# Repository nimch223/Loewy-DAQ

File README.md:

# Loewy-DAQ
  
Visit our research group website: https://www.lehighloewyinstitute.org  

**Loewy-DAQ** Contains the work of Lehigh University Loewy Institute undergraduate researcher Nicholas Cheney on the development of a chatter monitoring / DAQ system for a 4-high rolling mill. This forms the basis of a project which will be iterated on by future students; the idea is to make use of signal processing in combination with the metal rolling process in order to detect, predict, and respond to incidences of chatter. 

"Guide for Next User" follows, below: 

---
# **Guide for Next User - Vibrational Analysis for a Four-High Rolling Mill**
### **Author**: Nicholas Cheney @nimch223  
### **Advisors**: Professor Wojtek Misiolek & Nick Rockwell @nmrockwell 
### **Document Last Updated On**: January 15, 2024

---

# **Table of Contents:**
+ **[Background](#background)**
+ **[I. Set Up Hardware](#i-set-up-hardware)**  
+ **[II. Download Software: MATLAB & Simulink](#ii-download-software-matlab--simulink)**  
+ **[III. Open & Configure Software](#iii-open--configure-software)**  
+ **[IV. Run Software](#iv-run-software)**  
+ **[V. Additional Information & Future Recommendations](#v-additional-information--future-recommendations)**  
+ **[Papers Referenced](#papers-referenced)**

---

## Background  
Using two ADXL345 accelerometers connected to an Adafruit METRO (a microcontroller that
is equivalent to the Arduino Uno), vibrational analysis of a four high rolling mill can be
performed. The two accelerometers in their housings are to be mounted on the upper backup
roll and top housing of the rolling mill in Whitaker 165.
  
 These two locations for the placement of
the accelerometers were chosen based on a literature review in which it was discovered that
the upper backup roll and top housing demonstrate a higher sensitivity to chatter, making them
ideal locations for the permanent installation of acceleration sensors [Niroomand et al. 864].
  
The accelerometers measure the vertical vibration of the mill for the presence of chatter, the
intense and undesirable vibration of the mill that can negatively impact the rollers and affect
the quality of the rolled material. The most destructive forms of chatter occur at the third and
fifth octave modes of vibration, 100 - 200 Hz and 500 - 700 Hz respectively [Choudhary et al.
1].   

At third octave chatter conditions, the rolled sample experiences poor surface finish quality
and variations in thickness, while at fifth octave chatter conditions the sample experiences
even worse surface finish, larger variations in thickness and potential rupture of the sample,
and the backup and work rolls can experience transverse bending. 

The goal in installing these
vibrational sensors on the rolling mill in Whitaker 165 is to better understand the relationship
between the vibration of a one-stand mill and the quality of rolled samples, and if chatter
occurs, catch it with live vibrational monitoring before it becomes destructive to the sample and
rolls. The following document goes through the process of procuring, manufacturing, and
setting up the hardware for the vibrational sensors, and walks through the steps of how to
configure and run the software for plotting the vibrational data from the two accelerometers. 

--- 

## I. Set Up Hardware  

The following components outline the hardware used to make the vibrational sensor. Included
are either the links of where to find and buy them, or the files where they can be located.  

Files located in Github, at the following location: https://github.com/nimch223/Loewy-DAQ

**1. Microcontroller:**  
- Adafruit METRO 
  - Link: https://www.adafruit.com/product/2488
- Clear Housing for METRO
  - Link: https://www.adafruit.com/product/3597?gad_source=1&gclid=Cj0KCQiAm
4WsBhCiARIsAEJIEzXbmyYK6P6f_sxl3pgHApCRhQQjLrS05EgrbCzs6rN
KPTvZjAyUd0QaAgsNEALw_wcB

**2. Accelerometers:**  
- (x2) Adafruit ADXL345 Accelerometers
  - Link: https://www.adafruit.com/product/1231  

- (x2) 3D-Printed Housing for ADXL345  
  - These housings were designed in SolidWorks to perfectly fit the ADXL345, as no
CAD files could be found online for the current ADXL345 accelerometer model.
Two housings were then printed out of PLA in Wilbur Powerhouse using the FDM
printers.

    - STL File (in this Github repo) for 3D printing: **ADXL345_housing.STL**
    - SolidWorks File (also in this Github repo)--if needed to edit: **ADXL345_housing.SLDPRT**  

- (x4) Screws needed to secure each ADXL345 in housing

**3. Printed Circuit Board (PCB):**  
- The PCB was designed in Autodesk EAGLE, a free and intuitive PCB design software.
The physical board was then manufactured in the Electronics Design Lab in Wilbur
Powerhouse using the Othermill V2 CNC Mill. Using the soldering iron in Wilbur, four
10kΩ resistors and break-away male headers were soldered onto the board, shown in
**Figure 6**.

    - Autodesk EAGLE Files (in this Github repository):
      - Schematic File: **PCB_for_ADXL345.sch**  
      - Board File: **PCB_for_ADXL345.brd**

**4. Wires / Cables:**
- (x4) female-to-male (F/M) jumper wires - used to connect the Arduino to one side of the PCB.
  - These can be seen in **Figure 7**, labeled "3".
    - Link: https://www.adafruit.com/product/1953?gad_source=1&gclid=Cj0KCQiAm4WsBhCiARIsAEJIEzUyF3oqaQGZTwtKFuOSnZRV7XU1m5S8ml8urbqnD2HHYeW__Y-boksaAtEdEALw_wcB

- (x2) female-to-female (F/F) cables.
  - Each cable is roughly 5.5 feet and has 6 female header contacts on each side. Each cable is used to connect the 6 pins on the ADXL345 accelerometer (highlighted in **Figure 2**) to the respective header
on the PCB (labeled "ADXL345_1" and "ADXL345_2" on the schematic in **Figure 5**).
These were spliced and made in the electronics lab in Wilbur Powerhouse.

---

## II. Download Software: MATLAB & Simulink  

1. Open the following link: https://matlab.mathworks.com/  
2. Click "Install MATLAB", located at the top right of the page.  
3. Double-click the ".dmg" file that is downloaded onto your ocmputer and follow the steps to finish installation. 
- When asked, install both "MATLAB" and "Simulink". 
- When "Installation Complete" message appears, if prompted, install a supported C compiler for your machine by clicking the link.
  - For Macintosh users, you need at least **Xcode 14.x**
    - For Apple users:
      - Visit https://developer.apple.com/download/more/ and sign into Apple ID.
      - In the search bar, look up "Xcode"
      - Download the most recent version, or the most recent version supported by your machine (for me, Xcode 14.2)
        - Check minimum requirements here: https://developer.apple.com/support/xcode/
      - Launch Xcode, install necessary elements.

---  

## III. Open & Configure Software  

1. Double-click MATLAB to open the program.
2. In the main MATLAB window, search the top toolbar for "Add-Ons" and double-click it to select it. This is highlighted below in **Figure 8**:

3. The "Add-On Explorer" window should launch--use the search bar towards the top right, and search for "Arduino".
4. Pluf the microcontroller (METRO / Arduino) into the computer. Ensure it is getting power by making sure the onboard LED is lit.
5. Install the two support packages titled "Simulink Support Package for Arduino Hardware" and "MATLAB Support Package for Arduino Hardware" by clicking the respective titles, and selecting the "Add" blue button on the right side of the screen. Follow the instructions to download, and ensure that the microcontroller is recognized by the computer.
6. Once both support packages have been downloaded, they should have a green "Installed" message by their picture in the "Add-On Explorer", similar to the **Figure 9** below:  

7. Close the Add-On Explorer window.
8. In the main MATLAB window, search the top toolbar for "Simulink" and double-click it to launch. **Figure 10** below highlights the Simulink symbol in the toolbar:  

9. A new Simulink window should open.
10. Download the file titled **"Two_ADXL345_accell.slx"** from Github, and open the file in the Simulink window. The code should appear similar to **Figure 11** below:

11. In the Simulink window toolbar, verify that the following settings are configured as follows:
  - Under the "Simulation" tab, set "Stop Time" to "inf" (infinity)
  - Under the "Hardware" tab:
    - Select the "Hardware Board" dropdown menu, and click "Select Another Hardware Board". A "Configuration Parameters" window will appear, and in the "Hardware Implementation" tab, select the "Hardware board:" dropdown meny and select "Arduino Uno". Click "Apply" at the bottom right, then click "OK".
    - Ensure that the mode "Run on board" is selected.
    - Click on "Hardware Settings", and a "Configuration Parameters" window will appear. In the "Hardware Impplementation" tab, select the dropdown menu titled "Target hardware resources" nested in "Hardware board settings". Under the "Groups" ttle, select the "Host-board connection" tab.
    - Open your computer's terminal and type the following command:  
      `ls/vex/tty.*`
      This lists all the serial devices plugged into the computer. The Metro/Arduino should appear as the two serial ports:
      `/dev/tty.SLAB_USBtoUART` and `/dev/tty.usbserial-01C6018D`
      ...the latter, ending with "...018D", is the important one.
    - In the same "Host-board connection" tab, click the dropdown menu for "Set host COM port" and select "Manually select". Directly beneath in the "Host COM Port" dropdown, select `/dev/tty.usbserial-01C6018D/`. Ensure that it is the **`/dev/tty...`** selection and *NOT* the similarly named `/dev/cu...`.
    - Under the same "Groups" title, select the last tab, titled "External mode". Ensure the "Communication interface" dropdown selection is "XCP on Serial".

---  
## IV. Run Software  

1. Navigate back to the MATLAB main window.  
2. Type the following code into the editor window, labeled in Figure 12 below as (1), and then click "Run" labaled as (2):
    
```matlab
% MATLAB commands:
clear all;
clc;
clear a;
a = arduino; 
```

3. Navigate back to the Simulink window and click "Monitor & Tune" at the top.
4. The code will take some time to run; if it runs successfully, a "Stop" option will appear in the "Hardware" tab of the top toolbar, and "Data Inspector" to the right of it.
5. Click on Data Inspector and a "Simulation Data Inspector" window will appear. Initially, the data coming from the two accelerometers may be displayed on a single graph as 6 lines: "x", "y", and "z" data from each accelerometer.
6. To split the data from the two different accelerometers into two graphs, click the window icon, shown below in Figure 13 as the box highlighted and labeled as (1). Next, under "Basic layouts", select the option with a graph above and below, labeled (2) in **Figure 13** below:

7. Click the top graph, which is outlined in blue in Figure 14. Under the "Filter signals" dropdown menu on the left, select the checkbox of the 3rd signal from the 1st accelerometer. Ensure that all other signals are deselected. The "Simulation Data Inspector" window should appear in **Figure 14** below:

8. Click the bottom graph, then under the "Filter signals" dropdown menu on the left, select the checkbox of the 3rd signal from the 2nd accelerometer. Ensure that all other signals are deslected. The "Simulation Data Inspector" window should appear like **Figure 15** below:

9. Steps "7" and "8" ensure that only the z-axis (vertical) signal from each accelerometer is graphed. The two running graphs should now display vertical vibrational data from each accelerometer.
10. When finished with measuring the vibrational data, go to the Simulink window and click "Stop" in the toolbar.
11. To save the data from the graphs, go back to the "Simulation Data Inspector" window, and select the "Export" symbol on the left toolbar, shown in **Figure 16** below:

12. In the "Export" settings window:
    - For "Export:", choose to export only the "Selected runs and signals" for export.
    - For "To:", export the data as an Excel Workbook ".xlsx" file
    - Once the file is exported, the data should appear in your computer under the "MATLAB" folder, wherever that is located.  
  
---  
## V. Additional Information & Future Recommendations  

- The current Simulink code here on Githbu (**Two_ADXL345_accell.slx**) is relatively simple. As displayed in **Figure 11**, it is composed of two accelerometer data source blocks. These blocks are connected to a scope block, which allows for real time data visualization and the real time plotting of the vibrational data.
- These data source blocks are configured so that each block matches the respective I2C address of each accelerometer: **0x1D** and **0x53**.
  - The two accelerometers hooked up in the circuit are recognized under different addresses because one accelerometer's **SDO** pin is connected to **GND**, while the other accelerometer's **SDO** pin is not. This can be seen in **Figure 5** (the PCB schematic).
  - Double-click each accelerometer data source block to display these addresses
  - Double-clicking these blocks also displays additional parameters for the accelerometers that can be set. These parameters include important factors such as the range of acceleration that the accelerometers can measure, and the accelerometer output data rate. *These parameters should be adjusted based on further research and needs*.
  - For example, the accelerometer output data rate is automatically set at 12.5 Hz, which is not high enough for fast and accurate data streaming. The data rate can be adjusted to as high as 1600 Hz.
- This information regarding how the wiring of the pins should be configured in order to communicate with two accelerometers under two different I2C addresses was found in the ADXL345 data sheet. This data sheet, along with the Adafruit ADXL345 website that has pinout, wiring guides, example code, and more, are extremely informative and useful for understanding the capabilities and limitations of the accelerometers. The links are below:
  - ADXL345 Data Sheet: https://www.analog.com/media/en/technical-documentation/data-sheets/adxl345.pdf
 
  - ADXL345 webpage listing: https://learn.adafruit.com/adxl345-digital-accelerometer/overview  

- The need for additional processing, filtering, or denoising of the data may be discovered in the future. The MATLAB and Simulink software was chosen due to it being relatively simple, visual, and intuitive, and an easy base to build off of.
- In order to perform this additional data processing in Simulink, extra blocks would be added to the current Simulink model.
  - Based on the processing needs, pre-built data filtering blocks can be selected from Simulink's library.
  - These filtering blocks can be easily inserted between the accelerometer data source blocks and scope blocks--some examples of filter blocks that can be added are:
    - High pass filter block
    - Automatic gain control block
    - Low pass filter block
  - From the literature review, the aforementioned filters are recommended for data processing [Niroomand et al. 857]. **Figure 17** below shows a potential block diagram for data signal filtering and processing:

  - The process for the ADXL345 accelerometer would be similar to the process shown in **Figure 17** bit slightly different, as the accelerometers have a built in ADC, or "Analog to Digital (A/D) Converter".     
---  

## Papers Referenced  

1. Choudhary et al. “A Review on Chatter Analysis in Cold Rolling process.” Juniper Online
Journal Material Science, vol. 2, issue no. 1, 2017, page 1, ISSN 2575-856X.  

2. Niroomand et al. “Frequency analysis of chatter vibrations in tandem rolling mills.” Journal of
Vibroengineering, vol. 14, issue no. 2, 2012, pages 857 - 864, ISSN 1392-8716.

---

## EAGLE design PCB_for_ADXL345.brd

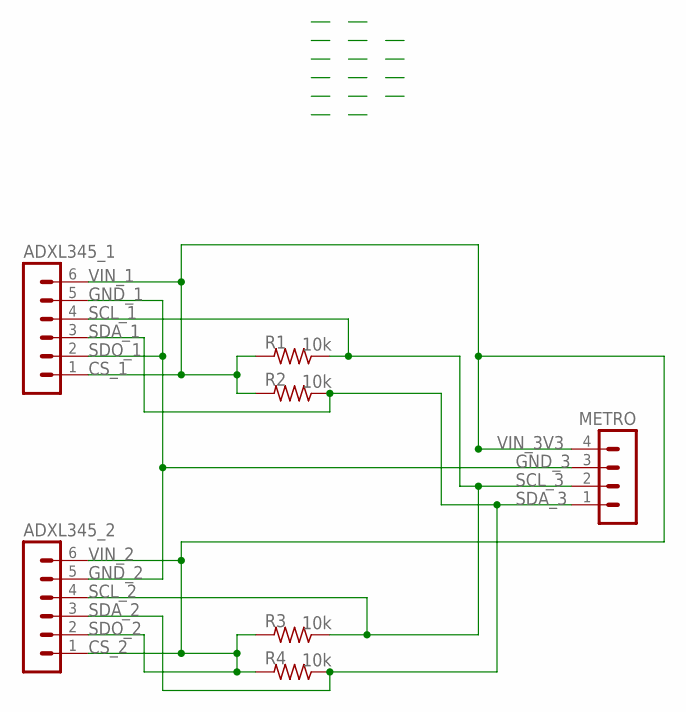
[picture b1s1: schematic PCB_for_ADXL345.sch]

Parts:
ADXL345_1, ADXL345_2: MA06-1
METRO: MA04-1
R1, R2, R3, R4: 10k; 0207/10

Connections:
GND: ADXL345_1.2, ADXL345_1.5, ADXL345_2.5, METRO.3
unnamed: ADXL345_1.3, ADXL345_2.3, METRO.1, R2.1, R4.1
unnamed: ADXL345_1.4, ADXL345_2.4, METRO.2, R1.1, R3.1
VIN: ADXL345_1.1, ADXL345_1.6, ADXL345_2.1, ADXL345_2.2, ADXL345_2.6, METRO.4, R1.2, R2.2, R3.2, R4.2

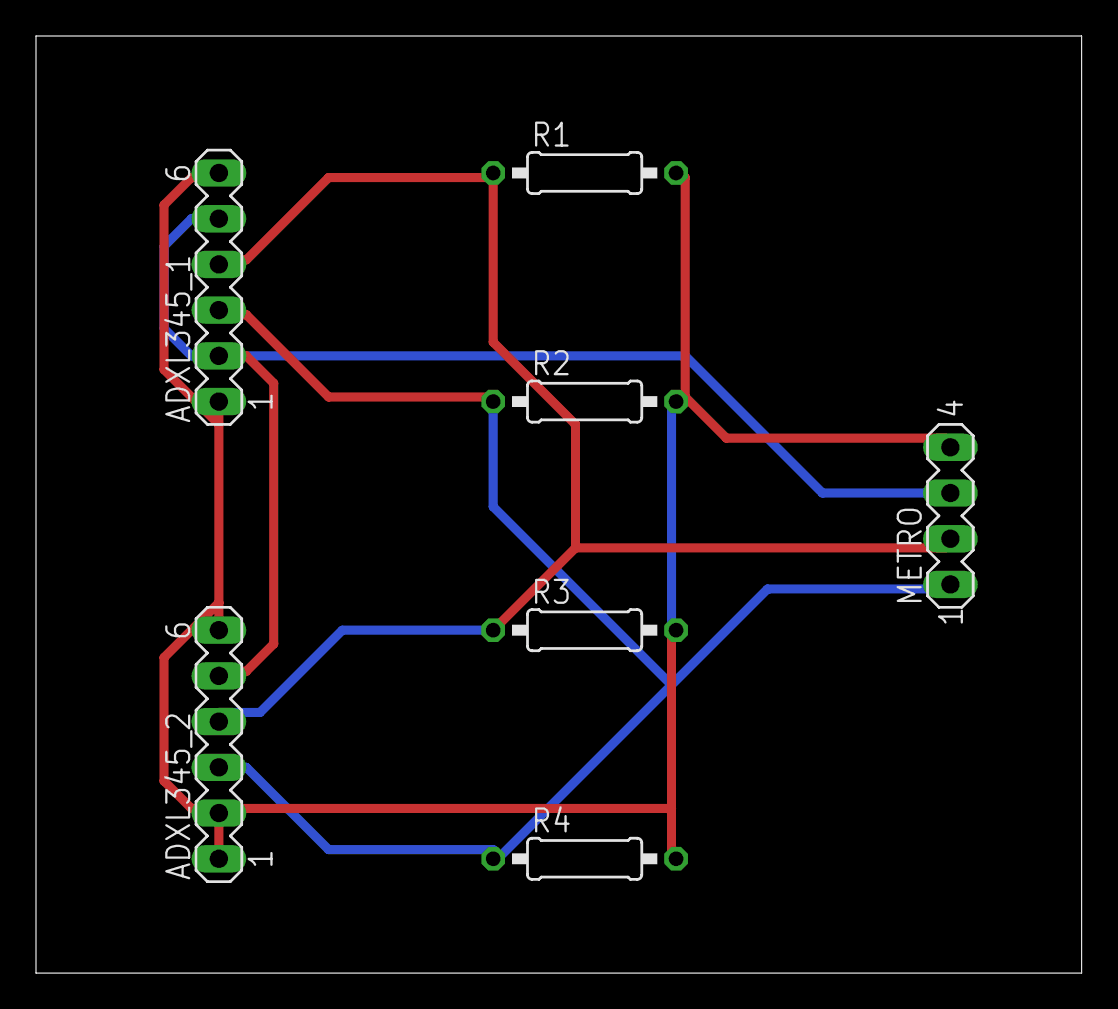
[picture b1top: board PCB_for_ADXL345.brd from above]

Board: 2 copper layers, 58.1 x 52.1 mm, 7 parts (0 on the bottom side), 4 nets.

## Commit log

2024-01-15 Add README.md contents from initial repo.
    Here we have copied the markdown version of the research report into the README.md file on this repo.
2024-01-15 Add background files for DAQ
    Added SolidWorks files for housing for DAQ device as well as Simulink file and EAGLE files.
2024-01-15 Add figures / images from research report
    This commit involves adding the figures referenced in the research report into the "img" folder.
2024-01-15 Adding github link to README.md
    Specifying where the background files are located in Github with the Github link
2024-01-15 Date Update README.md
    Changed the "Document Last Updated Section
